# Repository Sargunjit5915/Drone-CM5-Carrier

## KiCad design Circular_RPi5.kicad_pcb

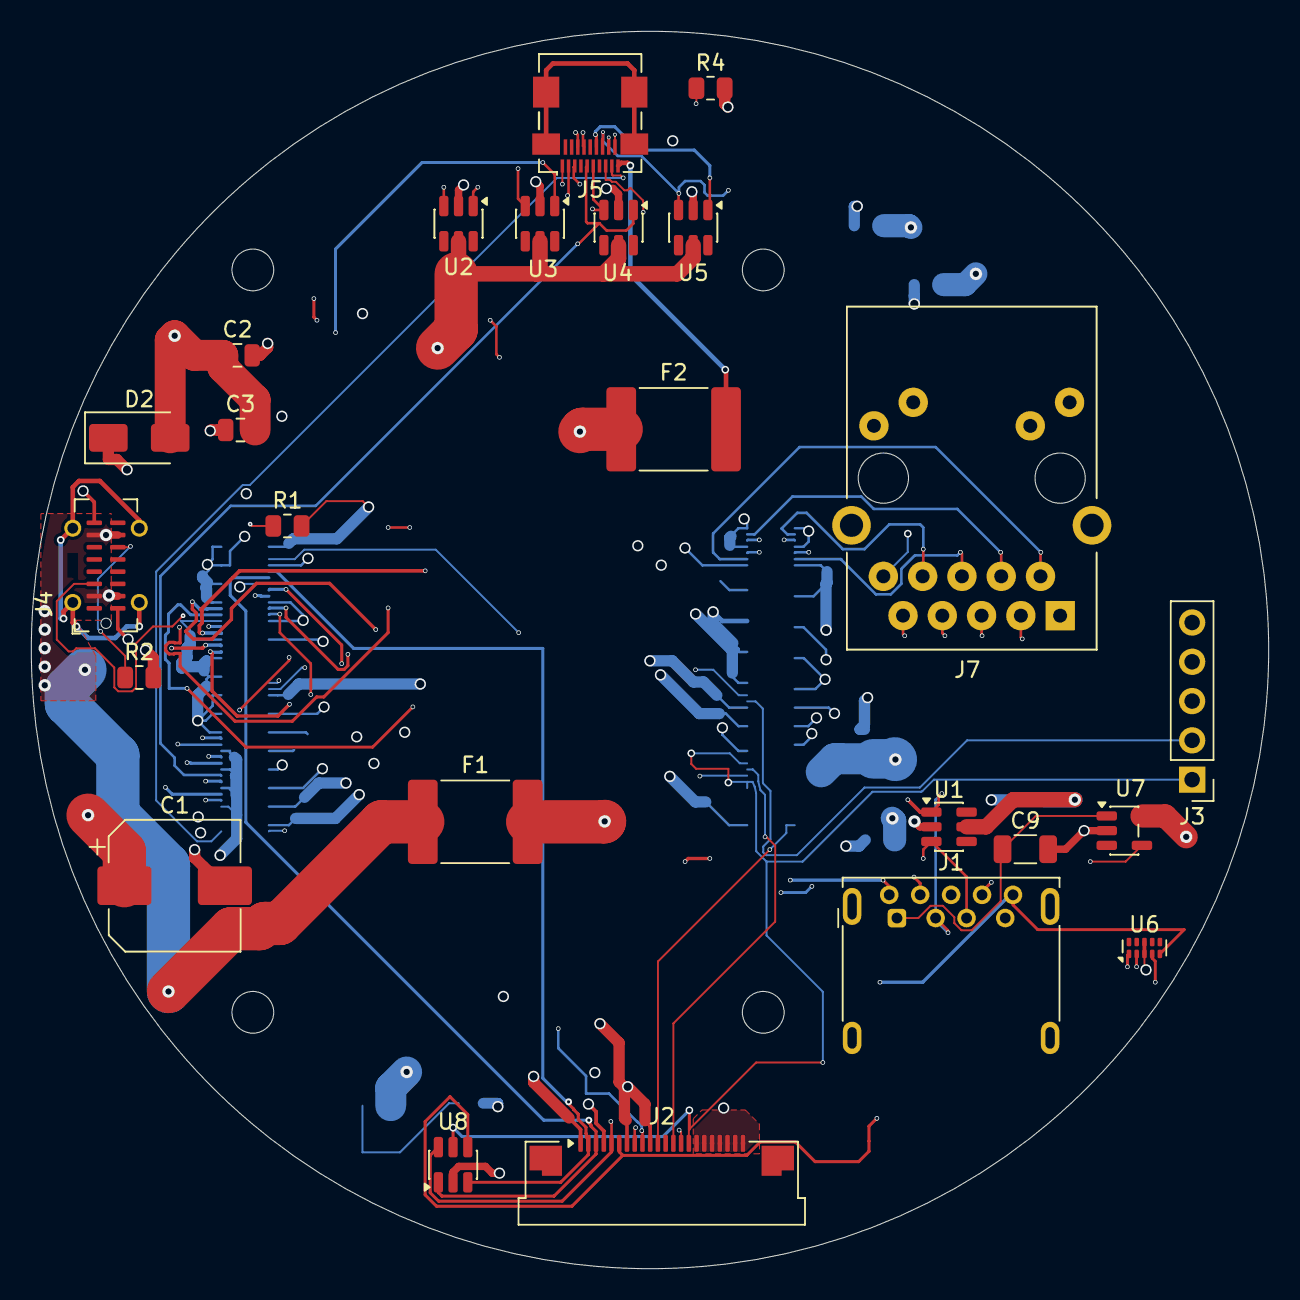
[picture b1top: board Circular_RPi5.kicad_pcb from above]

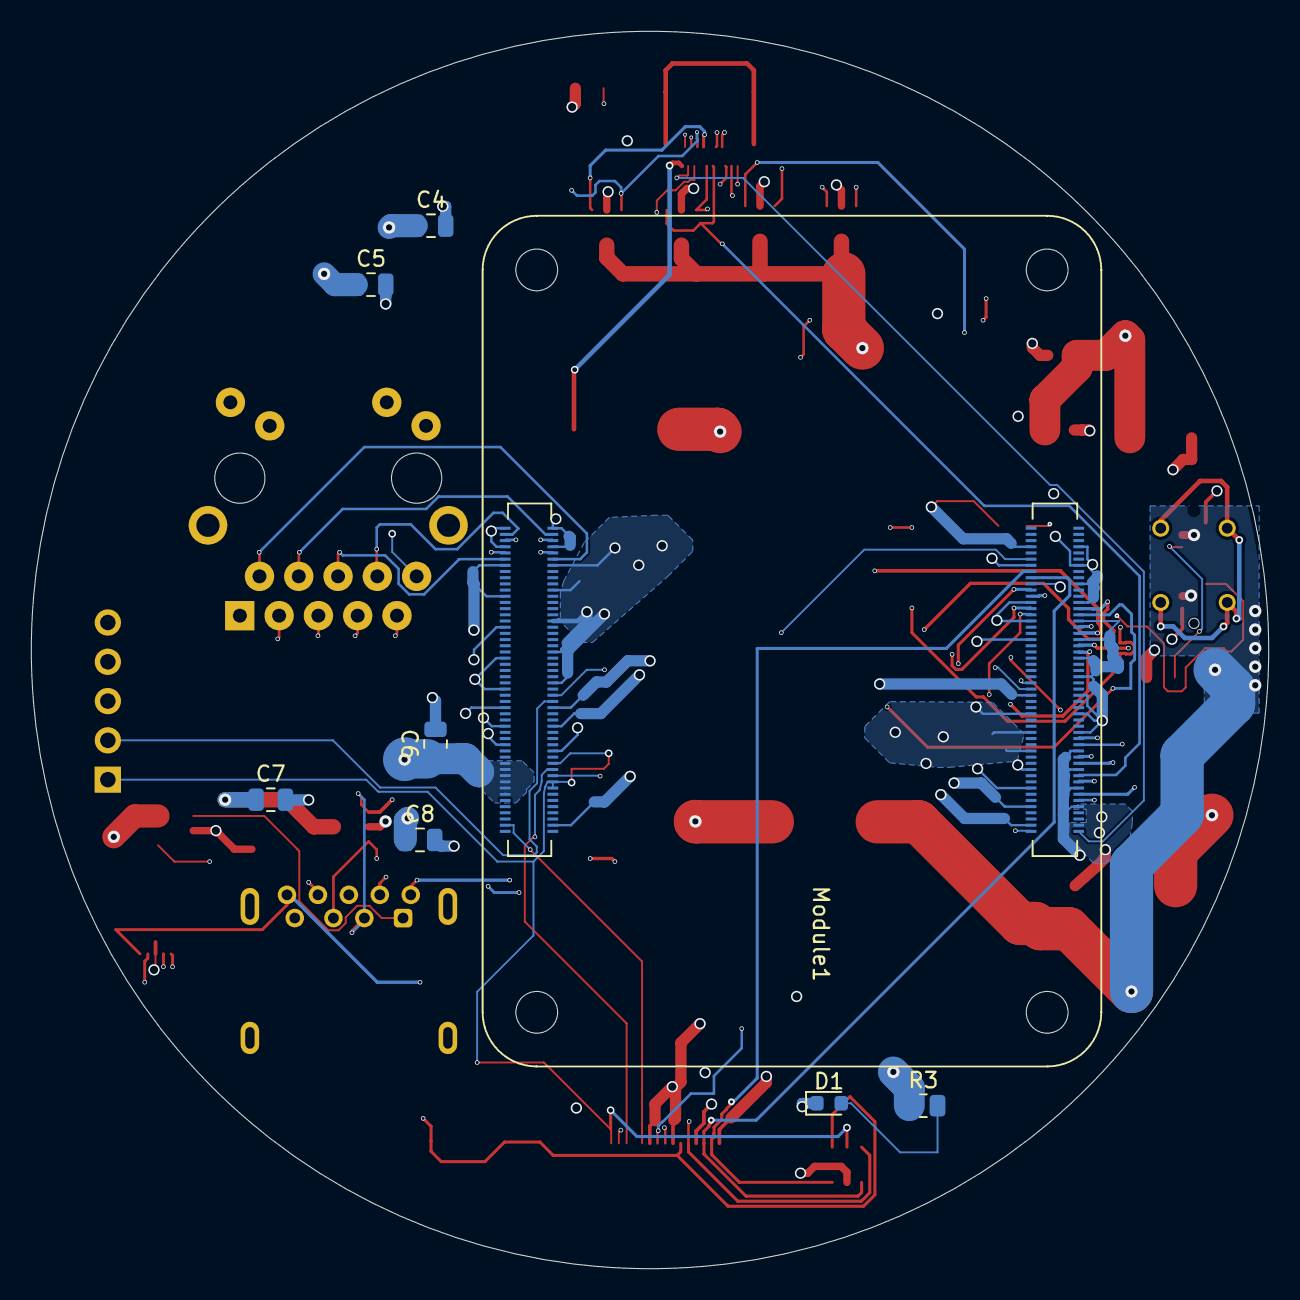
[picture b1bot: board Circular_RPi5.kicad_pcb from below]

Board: 6 copper layers, 80.0 x 80.0 mm, 32 parts (8 on the bottom side), 47 nets.

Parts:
C1: 470uF; CP_Elec_8x10
C2: 10uF; C_0805_2012Metric
C3, C4, C5, C6, C7, C8: 0.1uF; C_0805_2012Metric
C9: 22uF; C_1206_3216Metric
D1: LED; LED_0603_1608Metric
D2: D_TVS; D_SMA
F1, F2: 2920L500/16MR; Fuse_2920_7451Metric
J1: USB3_A; USB3_A_Molex_48393-001
J2: Conn_01x22; Amphenol_F32Q-1A7x1-11022_1x22-1MP_P0.5mm_Horizontal
J3: GPIO Pins; PinHeader_1x05_P2.54mm_Vertical
J4: USB_C; USB_C_Receptacle_G-Switch_GT-USB-7051x
J5: HDMI_D_1.4; HDMI_Micro-D_Molex_46765-0xxx
J7: RJ45_RB1-125B8G1A; RJ45_UDE_RB1-125B8G1A
Module1: ComputeModule5-CM5; Raspberry-Pi-5-Compute-Module
R1, R2: 5.1k; R_0805_2012Metric
R3: 330 ohm; R_0805_2012Metric
R4: 47k ohm; R_0805_2012Metric
U1, U2, U3, U4, U5, U8: USBLC; SOT-23-6
U6: TPD; USON-10_2.5x1.0mm_P0.5mm
U7: TPS; SOT-23-5

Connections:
+5V: C1.1, C2.1, C3.2, C4.1, C5.1, C6.1, C7.1, C8.1, D2.2 (A2), F1.2, F2.1, J3.5, Module1.77 (+5v_(Input)), Module1.79 (+5v_(Input)), Module1.81 (+5v_(Input)), Module1.83 (+5v_(Input)), Module1.85 (+5v_(Input)), Module1.87 (+5v_(Input)), R3.1, U1.5 (VBUS), U2.5 (VBUS), U3.5 (VBUS), U4.5 (VBUS), U5.5 (VBUS), U7.5 (IN)
/+3.3V: J2.15, J3.1, Module1.78 (GPIO_VREF(1.8v/3.3v_Input)), Module1.84 (+3.3v_(Output)), Module1.86 (+3.3v_(Output)), U8.5 (VBUS)
/CAM_GPIO0: J2.11, Module1.97 (CAM_GPIO0)
/Ethernet_Pair0_N: J7.R3, Module1.10 (Ethernet_Pair0_N)
/Ethernet_Pair0_P: J7.R2, Module1.12 (Ethernet_Pair0_P)
/Ethernet_Pair1_N: J7.R5, Module1.6 (Ethernet_Pair1_N)
/Ethernet_Pair1_P: J7.R4, Module1.4 (Ethernet_Pair1_P)
/Ethernet_Pair2_N: J7.R7, Module1.9 (Ethernet_Pair2_N)
/Ethernet_Pair2_P: J7.R6, Module1.11 (Ethernet_Pair2_P)
/Ethernet_Pair3_N: J7.R9, Module1.5 (Ethernet_Pair3_N)
/Ethernet_Pair3_P: J7.R8, Module1.3 (Ethernet_Pair3_P)
/GPIO2: J3.2, Module1.58 (GPIO2)
/GPIO3: J3.3, Module1.56 (GPIO3)
/HDMI0_CEC: J5.15 (CEC), Module1.151 (HDMI0_CEC)
/HDMI0_CLK_N: J5.14 (CK-), Module1.190 (HDMI0_CLK_N), U5.3 (I/O2)
/HDMI0_CLK_P: J5.12 (CK+), Module1.188 (HDMI0_CLK_P), U5.1 (I/O1)
/HDMI0_HOTPLUG: J5.1 (HPD/HEAC-), Module1.153 (HDMI0_HOTPLUG), R4.1
/HDMI0_SCL: J5.17 (SCL), Module1.200 (HDMI0_SCL)
/HDMI0_SDA: J5.18 (SDA), Module1.199 (HDMI0_SDA)
/HDMI0_TX0_N: J5.11 (D0-), Module1.184 (HDMI0_TX0_N), U4.3 (I/O2)
/HDMI0_TX0_P: J5.9 (D0+), Module1.182 (HDMI0_TX0_P), U4.1 (I/O1)
/HDMI0_TX1_N: J5.8 (D1-), Module1.178 (HDMI0_TX1_N), U3.3 (I/O2)
/HDMI0_TX1_P: J5.6 (D1+), Module1.176 (HDMI0_TX1_P), U3.1 (I/O1)
/HDMI0_TX2_N: J5.5 (D2-), Module1.172 (HDMI0_TX2_N), U2.3 (I/O2)
/HDMI0_TX2_P: J5.3 (D2+), Module1.170 (HDMI0_TX2_P), U2.1 (I/O1)
/MIPI0_C_N: J2.8, Module1.127 (MIPI0_C_N)
/MIPI0_C_P: J2.9, Module1.129 (MIPI0_C_P)
/MIPI0_D0_N: J2.2, Module1.115 (MIPI0_D0_N), U8.3 (I/O2)
/MIPI0_D0_P: J2.3, Module1.117 (MIPI0_D0_P), U8.1 (I/O1)
/MIPI0_D1_N: J2.5, Module1.121 (MIPI0_D1_N), U8.6 (I/O4)
/MIPI0_D1_P: J2.6, Module1.123 (MIPI0_D1_P), U8.4 (I/O3)
/SCL0: J2.13, Module1.80 (SCL0)
/SDA0: J2.14, Module1.82 (SDA0)
/SSRX+: J1.6, Module1.130 (USB3-0-RX_P), U6.4 (D2+)
/SSRX-: J1.5, Module1.128 (USB3-0-RX_N), U6.5 (D2-)
/SSTX+: J1.9, Module1.142 (USB3-0-TX_P), U6.1 (D1+)
/SSTX-: J1.8, Module1.140 (USB3-0-TX_N), U6.2 (D1-)
/USB3-0-D_N: J1.2, Module1.136 (USB3-0-D_N), U1.1 (I/O1)
/USB3-0-D_P: J1.3, Module1.134 (USB3-0-D_P), U1.3 (I/O2)
/VBUS_EN: Module1.111 (VBUS_EN), U7.4 (EN)
/VBUS_IN: F1.1, J4.A4, J4.A9 (VBUS), J4.B4, J4.B9 (VBUS)
GND: C1.2, C2.2, C3.1, C4.2, C5.2, C6.2, C7.2, C8.2, C9.2, D1.1 (K), D2.1 (A1), J1.4, J1.7, J1.10, J2.1, J2.4, J2.7, J2.10, J2.16, J2.17, J2.18, J2.19, J2.20, J2.21, J2.22, J3.4, J4.A12 (GND), J4.B12 (GND), J5.16 (GND), J7.R10, J7.SH, Module1.1 (GND), Module1.2 (GND), Module1.7 (GND), Module1.8 (GND), Module1.13 (GND), Module1.14 (GND), Module1.22 (GND), Module1.23 (GND), Module1.32 (GND), Module1.33 (GND), Module1.42 (GND), Module1.43 (GND), Module1.52 (GND), Module1.53 (GND), Module1.59 (GND), Module1.60 (GND), Module1.65 (GND), Module1.66 (GND), Module1.71 (GND), Module1.74 (GND), Module1.98 (GND), Module1.107 (GND), Module1.108 (GND), Module1.113 (GND), Module1.114 (GND), Module1.119 (GND), Module1.120 (GND), Module1.125 (GND), Module1.126 (GND), Module1.131 (GND), Module1.132 (GND), Module1.137 (GND), Module1.138 (GND), Module1.144 (GND), Module1.150 (GND), Module1.155 (GND), Module1.156 (GND), Module1.161 (GND), Module1.162 (GND), Module1.167 (GND), Module1.168 (GND), Module1.173 (GND), Module1.174 (GND), Module1.179 (GND), Module1.180 (GND), Module1.185 (GND), Module1.186 (GND), Module1.191 (GND), Module1.192 (GND), Module1.197 (GND), Module1.198 (GND), R1.2, R2.2, R4.2, U1.2 (GND), U2.2 (GND), U3.2 (GND), U4.2 (GND), U5.2 (GND), U6.3 (GND), U6.8 (GND), U7.2 (GND), U8.2 (GND)
unnamed: D1.2 (A), R3.2
unnamed: C9.1, J1.1, U7.1 (OUT)
unnamed: J4.A5 (CC1), R1.1
unnamed: J4.B5 (CC2), R2.1
unnamed: F2.2, J5.19 (+5V)

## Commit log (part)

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2026-02-18 Initial stable 8-layer design - DRC Clean
2026-02-18 cm5.pretty file added
2026-02-18 LED fixed
2026-02-23 PCB Fixed
2026-02-23 Reduced to 6 layers
